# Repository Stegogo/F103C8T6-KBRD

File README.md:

# KBRD

4-key arrow keyoard from scratch, based on STM32F103C8T6. Work in progress.

## Scematic and PCB

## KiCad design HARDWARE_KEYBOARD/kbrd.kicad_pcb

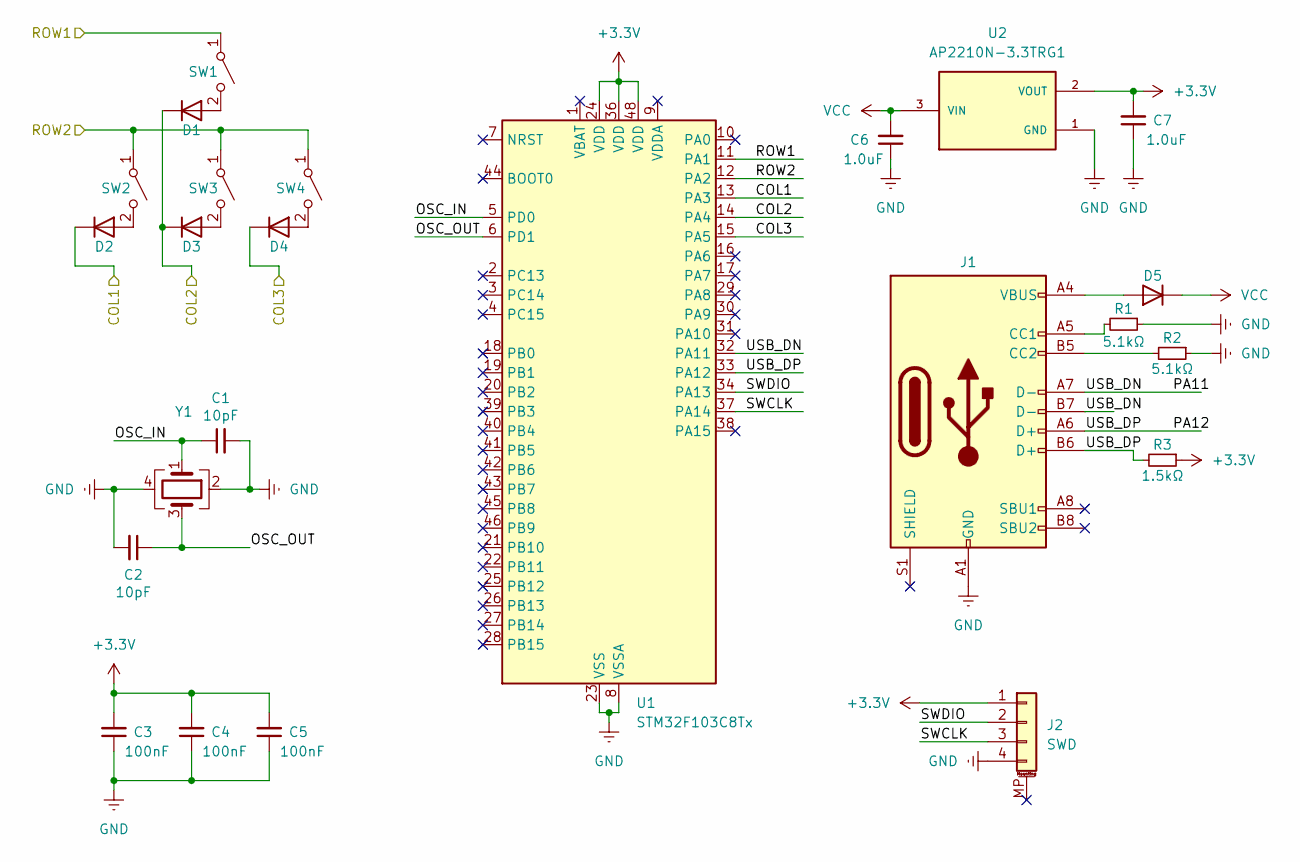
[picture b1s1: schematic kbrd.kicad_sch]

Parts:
C1, C2: 10pF; C_0603_1608Metric_Pad1.08x0.95mm_HandSolder
C3, C4, C5: 100nF; C_0603_1608Metric_Pad1.08x0.95mm_HandSolder
C6, C7: 1.0uF; C_0603_1608Metric_Pad1.08x0.95mm_HandSolder
D1, D2, D3, D4, D5: D; D_0603_1608Metric_Pad1.05x0.95mm_HandSolder
J1: USB_C_Receptacle_USB2.0_16P; USB_C_Receptacle_GCT_USB4105-xx-A_16P_TopMnt_Horizontal
J2: SWD; PinHeader_1x04_P2.00mm_Vertical
R1, R2: 5.1kΩ; R_0603_1608Metric_Pad0.98x0.95mm_HandSolder
R3: 1.5kΩ; R_0603_1608Metric_Pad0.98x0.95mm_HandSolder
SW1, SW2, SW3, SW4: SW_SPST; SW_Cherry_MX_PCB_1.00u
U1: STM32F103C8Tx; LQFP-48_7x7mm_P0.5mm
U2: AP2210N-3.3TRG1; SOT-23-3
Y1: Crystal_GND24; Oscillator_SMD_Abracon_ASV-4Pin_7.0x5.1mm

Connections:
+3.3V: C3.2, C4.2, C5.2, C7.2, J2.1, R3.1, U1.24 (VDD), U1.36 (VDD), U1.48 (VDD), U2.2 (VOUT)
/COL1: D2.1 (K), U1.13 (PA3)
/COL2: D1.1 (K), D3.1 (K), U1.14 (PA4)
/COL3: D4.1 (K), U1.15 (PA5)
/OSC_IN: C1.1, U1.5 (PD0), Y1.1
/OSC_OUT: C2.1, U1.6 (PD1), Y1.3
/PA11: J1.A7 (D-), J1.B7 (D-), U1.32 (PA11)
/PA12: J1.A6 (D+), J1.B6 (D+), R3.2, U1.33 (PA12)
/ROW1: SW1.1 (A), U1.11 (PA1)
/ROW2: SW2.1 (A), SW3.1 (A), SW4.1 (A), U1.12 (PA2)
/SWCLK: J2.3, U1.37 (PA14)
/SWDIO: J2.2, U1.34 (PA13)
GND: C1.2, C2.2, C3.1, C4.1, C5.1, C6.1, C7.1, J1.A1 (GND), J1.A12 (GND), J1.B1 (GND), J1.B12 (GND), J2.4, R1.1, R2.1, U1.8 (VSSA), U1.23 (VSS), U1.35 (VSS), U1.47 (VSS), U2.1 (GND), Y1.2, Y1.4
unnamed: D1.2 (A), SW1.2 (B)
unnamed: D2.2 (A), SW2.2 (B)
unnamed: D3.2 (A), SW3.2 (B)
unnamed: D4.2 (A), SW4.2 (B)
unnamed: D5.2 (A), J1.A4 (VBUS), J1.A9 (VBUS), J1.B4 (VBUS), J1.B9 (VBUS)
unnamed: J1.A5 (CC1), R1.2
unnamed: J1.B5 (CC2), R2.2
VCC: C6.2, D5.1 (K), U2.3 (VIN)

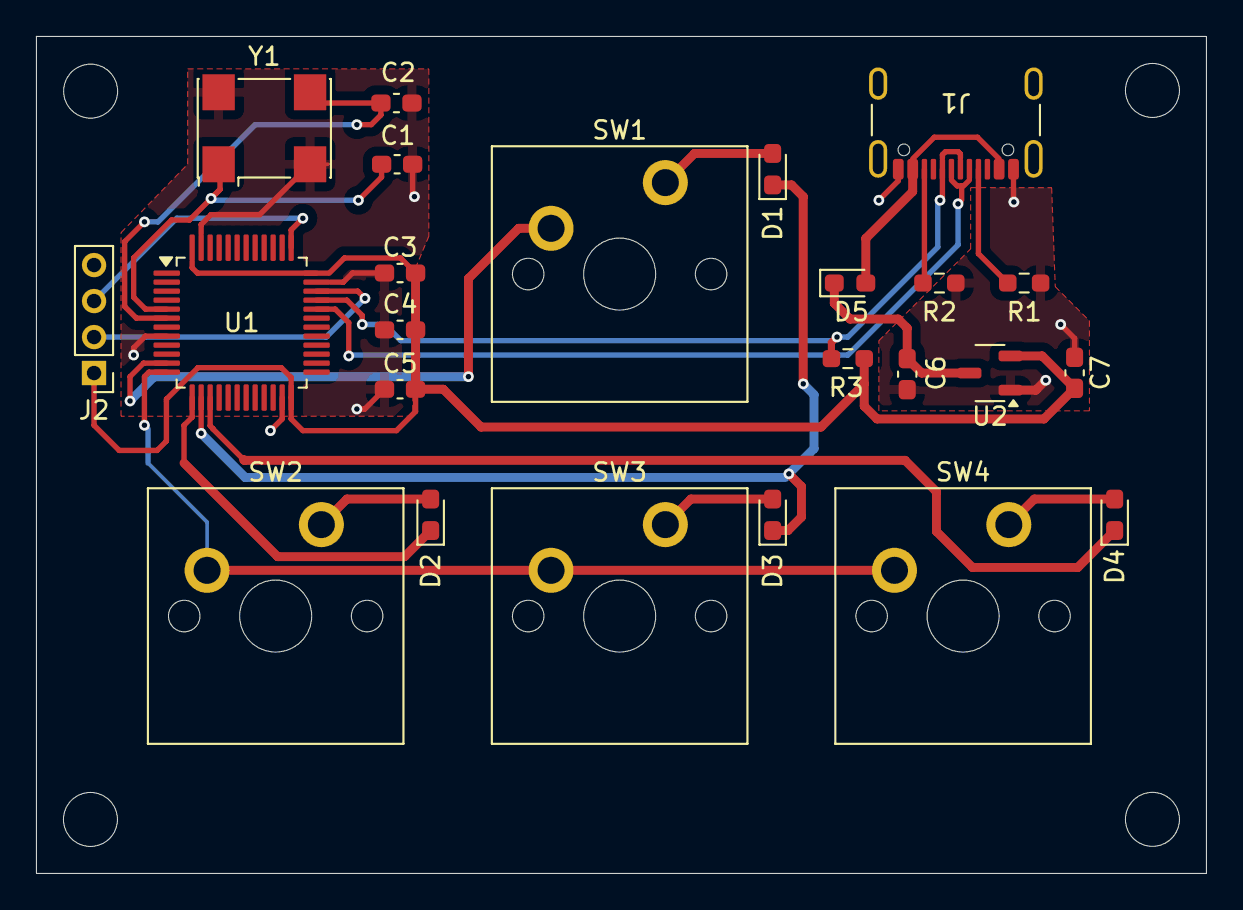
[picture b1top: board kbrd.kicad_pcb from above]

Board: 2 copper layers, 65.0 x 46.5 mm, 24 parts (0 on the bottom side), 21 nets.

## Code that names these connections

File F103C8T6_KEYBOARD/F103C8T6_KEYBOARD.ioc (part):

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Mcu.Name=STM32F103C(8-B)Tx
Mcu.Package=LQFP48
Mcu.UserName=STM32F103C8Tx
PA1.GPIOParameters=GPIO_Label
PA1.GPIO_Label=ROW1
PA1.Signal=GPIO_Output
PA11.Mode=Device
PA11.Signal=USB_DM
PA12.Mode=Device
PA12.Signal=USB_DP
PA13.Mode=Serial_Wire
PA13.Signal=SYS_JTMS-SWDIO
PA14.Mode=Serial_Wire
PA14.Signal=SYS_JTCK-SWCLK
PA2.GPIOParameters=GPIO_Label
PA2.GPIO_Label=ROW2
PA2.Signal=GPIO_Output
PA3.GPIOParameters=GPIO_Label
PA3.GPIO_Label=COL1
PA3.Signal=GPIO_Input
PA4.GPIOParameters=GPIO_Label
PA4.GPIO_Label=COL2
PA4.Signal=GPIO_Input
PA5.GPIOParameters=GPIO_Label
PA5.GPIO_Label=COL3
PA5.Signal=GPIO_Input
PB12.GPIOParameters=GPIO_Label
PB12.GPIO_Label=LED
PB12.Signal=GPIO_Output
PD0-OSC_IN.Mode=HSE-External-Oscillator
PD0-OSC_IN.Signal=RCC_OSC_IN
PD1-OSC_OUT.Mode=HSE-External-Oscillator
PD1-OSC_OUT.Signal=RCC_OSC_OUT
RCC.SYSCLKFreq_VALUE=48000000
RCC.SYSCLKSource=RCC_SYSCLKSOURCE_PLLCLK
board=custom

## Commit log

2024-10-05 Init repo
2024-10-05 Fix firmware folder
2024-10-06 Updated PCB & schematic
2024-10-06 Add README & images
2024-10-06 Remove unnecessary
2024-10-08 Add copper zones; remove extra GND traces
2024-10-09 Change track sizes
2024-10-09 Add IBOM
2024-10-09 Add gerber
2024-10-09 Chane volt regulator footprint to fit the one im going to use
2024-10-13 Add drill files
